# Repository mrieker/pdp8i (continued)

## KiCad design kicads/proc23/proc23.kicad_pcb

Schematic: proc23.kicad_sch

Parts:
J1, J2, J3, J4: Conn_01x36; PinHeader_1x36_P2.54mm_Vertical
U1, U11, U17, U18, U19, U35, U37, U46, U49, U50, U162, U163, U169: 74AHC540; DIP-20_W7.62mm
U8, U106, U119, U123, U124, U125, U128, U141: 74AHC04; DIP-14_W7.62mm
U21, U140: 74AHC138; DIP-16_W7.62mm
U27, U142, U144: 74AHC02; DIP-14_W7.62mm
U44, U82, U91, U107, U108, U109, U113, U120, U127, U147, U151, U156, U158, U161, U168: 74AHC00; DIP-14_W7.62mm
U54, U55, U56, U74, U77, U80: 74AHC08; DIP-14_W7.62mm
U57: 74AC11; DIP-14_W7.62mm
U58, U59, U60, U89: 74AHC86; DIP-14_W7.62mm
U61, U62, U65, U66, U69, U70, U83, U84, U85, U86, U87, U88: 74AC153; DIP-16_W7.62mm
U63, U64, U67: 74AHC157; DIP-16_W7.62mm
U68, U71, U116, U157, U165: 74HC30; DIP-14_W7.62mm
U73, U76, U79, U110: 74AHC32; DIP-14_W7.62mm
U75, U78, U81: 74AC283; DIP-16_W7.62mm
U90: 74AHC74
U92, U93, U94, U95, U96, U97, U98, U99, U100, U101, U102, U103, U104: 74AC151; DIP-16_W7.62mm
U105, U111, U112, U143, U146, U148, U149, U150, U159, U160: 74AC10; DIP-14_W7.62mm
U114: 74HC42; DIP-16_W7.62mm
U117, U118, U121, U122, U153, U164: 74AC20; DIP-14_W7.62mm
U126: 74AHC08
U129, U130, U131, U132, U136, U137: 74AHC174; DIP-16_W7.62mm
U133, U134, U135: 74AC161; DIP-16_W7.62mm
U138: 74AHC74; DIP-14_W7.62mm
U139: 74AC175; DIP-16_W7.62mm
U145, U152, U154, U170: 74HC27; DIP-14_W7.62mm
U155: 74HC21; DIP-14_W7.62mm
U171: 74HC4075; DIP-14_W7.62mm

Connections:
/AA: U27.2, U161.6, U170.9
/BB: U68.8, U125.11, U144.8
/CC: U144.9, U148.8
/CC3: U128.4, U168.9, U171.1
/CONSCK: J4.35
/CONSDA: J4.34
/EE: U27.8, U160.8
/FF: U27.9, U142.5, U144.6, U153.8
/HH: U106.12, U170.1, U170.3
/JJ: U142.6, U144.5, U165.8, U170.2, U170.4
/KK: U128.10, U170.10
/LL: U118.6, U170.13
/MM: U159.12, U170.5
/NN: U119.2, U156.9, U170.11
/PP: U161.11
/_AA1: U143.12, U161.4
/_AA2: U127.8, U161.5
/_ACCLEAR: J3.28, U50.4 (A2)
/_ACUM_0: J3.7, U46.16 (Y2)
/_ACUM_1: J2.34, U37.13 (Y5)
/_ACUM_2: J2.27, U37.18 (Y0)
/_ACUM_3: J2.20, U35.15 (Y3)
/_ACUM_4: J2.13, U19.12 (Y6)
/_ACUM_5: J2.7, U19.17 (Y1)
/_ACUM_6: J1.35, U18.14 (Y4)
/_ACUM_7: J1.29, U17.11 (Y7)
/_ACUM_8: J1.23, U17.16 (Y2)
/_ACUM_9: J1.16, U11.14 (Y4)
/_ACUM_10: J1.9, U1.12 (Y6)
/_ACUM_11: J1.2, U1.18 (Y0)
/_BB1: U68.3, U123.2
/_BB2: U68.4, U119.10
/_BB3: U68.5, U146.8
/_BB4: U68.6, U147.3
/_BB5: U68.11, U110.8
/_BB6: U68.12, U171.6
/_BRKCYC: J4.33, U163.11 (Y7)
/_BRKGNTI: J4.32
/_BRKGNTO: J4.31
/_BRKRQST: J3.29
/_BRKWRM: J4.11, U50.6 (A4)
/_BUSINI: J3.31, U163.3 (A1)
/_BWCOV: J3.32, U163.16 (Y2)
/_CAINC: J4.12, U50.7 (A5)
/_CC1: U109.11, U148.9, U168.12
/_CC2: U147.8, U148.10, U168.13
/_CC3: U110.4, U111.6, U128.3, U148.11
/_CLOCK: J4.6, U50.2 (A0)
/_CYCLE3: J4.13, U50.8 (A6)
/_DFLD_0: J3.22
/_DFLD_1: J3.18
/_DFLD_2: J3.14
/_DMAFLD_0: J3.23
/_DMAFLD_1: J3.19
/_DMAFLD_2: J3.15
/_EE1: U149.6, U160.9
/_EE2: U148.6, U160.10
/_EE3: U147.11, U160.11
/_FF1: U150.12, U153.9
/_FF2: U150.6, U153.10
/_FF3: U151.8, U153.12
/_FF4: U149.12, U153.13
/_HH1: U106.13, U142.1
/_IFLD_0: J3.24
/_IFLD_1: J3.20
/_IFLD_2: J3.16
/_INBUS_0: J3.10, U46.7 (A5)
/_INBUS_1: J3.3, U46.2 (A0)
/_INBUS_2: J2.30, U37.5 (A3)
/_INBUS_3: J2.23, U35.8 (A6)
/_INBUS_4: J2.16, U35.3 (A1)
/_INBUS_5: J2.10, U19.6 (A4)
/_INBUS_6: J2.4, U18.9 (A7)
/_INBUS_7: J1.32, U18.4 (A2)
/_INBUS_8: J1.26, U17.7 (A5)
/_INBUS_9: J1.19, U11.9 (A7)
/_INBUS_10: J1.12, U11.3 (A1)
/_INBUS_11: J1.5, U1.5 (A3)
/_INTINH: J4.15
/_INTRQST: J4.16
/_ION: J3.30, U163.2 (A0)
/_IOP: J4.8, U163.5 (A3)
/_IOSKIP: J4.17, U162.4 (A2)
/_IREG_9: J1.22, U17.17 (Y1)
/_IREG_10: J1.15, U11.15 (Y3)
/_IREG_11: J1.8, U1.13 (Y5)
/_JJ1: U127.6, U165.3
/_JJ2: U151.11, U165.4
/_JJ3: U146.6, U165.5
/_JJ4: U158.3, U165.6
/_JJ5: U158.6, U165.11
/_JJ6: U44.3, U165.12
/_KK1: U128.11, U159.6
/_LINK: J4.9, U163.14 (Y4)
/_LL1: U118.1, U146.12
/_LL2: U118.2, U158.8
/_LL3: U118.4, U158.11
/_LL4: U118.5, U160.12
/_LNKTOG: J4.18, U162.5 (A3)
/_MADR_0: J3.8, U46.15 (Y3)
/_MADR_1: J2.35, U37.12 (Y6)
/_MADR_2: J2.28, U37.17 (Y1)
/_MADR_3: J2.21, U35.14 (Y4)
/_MADR_4: J2.14, U19.11 (Y7)
/_MADR_5: J2.8, U19.16 (Y2)
/_MADR_6: J2.2, U18.13 (Y5)
/_MADR_7: J1.30, U18.18 (Y0)
/_MADR_8: J1.24, U17.15 (Y3)
/_MADR_9: J1.17, U11.13 (Y5)
/_MADR_10: J1.10, U1.11 (Y7)
/_MADR_11: J1.3, U1.17 (Y1)
/_MAJST_0: J4.22, U162.6 (A4)
/_MAJST_1: J4.21, U162.7 (A5)
/_MAJST_2: J4.20, U162.8 (A6)
/_MAJST_3: J4.19, U162.9 (A7)
/_MBUF_0: J3.9, U46.14 (Y4)
/_MBUF_1: J3.2, U37.11 (Y7)
/_MBUF_2: J2.29, U37.16 (Y2)
/_MBUF_3: J2.22, U35.13 (Y5)
/_MBUF_4: J2.15, U35.18 (Y0)
/_MBUF_5: J2.9, U19.15 (Y3)
/_MBUF_6: J2.3, U18.12 (Y6)
/_MBUF_7: J1.31, U18.17 (Y1)
/_MBUF_8: J1.25, U17.14 (Y4)
/_MBUF_9: J1.18, U11.12 (Y6)
/_MBUF_10: J1.11, U11.18 (Y0)
/_MBUF_11: J1.4, U1.16 (Y2)
/_MEAD_0: J3.25
/_MEAD_1: J3.21
/_MEAD_2: J3.17
/_MEMDIS: J3.26
/_MM1: U150.8, U159.1
/_MM2: U159.2, U161.3
/_MM3: U122.8, U159.13
/_MQUO_0: J3.11
/_MQUO_1: J3.4
/_MQUO_2: J2.31
/_MQUO_3: J2.24
/_MQUO_4: J2.17
/_MQUO_5: J2.11
/_MQUO_6: J2.5
/_MQUO_7: J1.33
/_MQUO_8: J1.27
/_MQUO_9: J1.20
/_MQUO_10: J1.13
/_MQUO_11: J1.6
/_NN1: U105.4, U119.1, U149.8
/_PAUSE: J4.14
/_PCTR_0: J3.12, U46.12 (Y6)
/_PCTR_1: J3.5, U46.17 (Y1)
/_PCTR_2: J2.32, U37.14 (Y4)
/_PCTR_3: J2.25, U35.11 (Y7)
/_PCTR_4: J2.18, U35.16 (Y2)
/_PCTR_5: J2.12, U19.13 (Y5)
/_PCTR_6: J2.6, U19.18 (Y0)
/_PCTR_7: J1.34, U18.15 (Y3)
/_PCTR_8: J1.28, U17.12 (Y6)
/_PCTR_9: J1.21, U17.18 (Y0)
/_PCTR_10: J1.14, U11.16 (Y2)
/_PCTR_11: J1.7, U1.14 (Y4)
/_PP1: U119.5, U159.8, U161.12
/_PP2: U105.3, U160.6, U161.13
/_READSR: J3.27, U46.11 (Y7)
/_RESET: J4.7, U50.3 (A1)
/_RUN: J4.10, U163.7 (A5)
/_SWCONT: J4.2, U49.5 (A3)
/_SWDEPOS: J3.35, U49.4 (A2)
/_SWEXAM: J3.34, U49.3 (A1)
/_SWLDAD: J3.33, U49.2 (A0)
/_SWSINST: J4.5
/_SWSSTEP: J4.4
/_SWSTART: J4.3, U49.6 (A4)
/_TP1: J4.27, U169.6 (A4)
/_TP2: J4.28, U169.7 (A5)
/_TP3: J4.29, U169.8 (A6)
/_TP4: J4.30, U169.9 (A7)
/_TS1: J4.23, U169.2 (A0)
/_TS2: J4.24, U169.3 (A1)
/_TS3: J4.25, U169.4 (A2)
/_TS4: J4.26, U169.5 (A3)
/_asel_0: U61.14 (S0), U62.14 (S0), U65.14 (S0), U66.14 (S0), U69.14 (S0), U70.14 (S0), U164.4, U170.12
/_asel_1: U61.2 (S1), U62.2 (S1), U65.2 (S1), U66.2 (S1), U69.2 (S1), U70.2 (S1), U164.5, U170.6
/_bsel_0: U63.1 (S), U64.1 (S), U67.1 (S), U144.10
/_clock: U8.4
/_extarex: U44.10, U112.11, U119.12, U121.13
/_irand: U140.15 (~Y0), U141.13, U143.9
/_irdca: U105.10, U140.12 (~Y3), U141.5, U143.11
/_iriot: U140.9 (~Y6)
/_irisz: U105.9, U140.13 (~Y2), U141.9
/_irjmp: U140.10 (~Y5), U141.1, U142.8
/_irjms: U105.11, U140.11 (~Y4), U141.3
/_iropr: U106.5, U122.13, U140.7 (~Y7), U144.2, U145.1
/_irtad: U140.14 (~Y1), U141.11, U143.10
/_ldadclk: U82.12, U111.1, U161.8
/_msdefer: U114.3 (2), U123.11
/_msdepos: U114.10 (8), U116.12, U124.11
/_msexec: U82.1, U114.4 (3), U123.13
/_msintak: U114.9 (7), U116.11, U118.13, U124.9
/_mswrdct: U82.2, U114.5 (4), U116.4, U124.1
/_nxtmsbreak: U21.9 (~Y6), U171.4
/_nxtmswrdct: U21.11 (~Y4), U110.10
/_pcld: U56.3, U133.9 (~PE), U134.9 (~PE), U135.9 (~PE)
/_reset: U8.6, U138.13 (~R)
/_rsel_0: U91.6, U92.11 (S0), U93.11 (S0), U94.11 (S0), U95.11 (S0), U96.11 (S0), U97.11 (S0), U98.11 (S0), U99.11 (S0), U100.11 (S0), U101.11 (S0), U102.11 (S0), U103.11 (S0), U104.11 (S0)
/_rsel_1: U91.8, U92.10 (S1), U93.10 (S1), U94.10 (S1), U95.10 (S1), U96.10 (S1), U97.10 (S1), U98.10 (S1), U99.10 (S1), U100.10 (S1), U101.10 (S1), U102.10 (S1), U103.10 (S1), U104.10 (S1)
/_rsel_2: U91.11, U92.9 (S2), U93.9 (S2), U94.9 (S2), U95.9 (S2), U96.9 (S2), U97.9 (S2), U98.9 (S2), U99.9 (S2), U100.9 (S2), U101.9 (S2), U102.9 (S2), U103.9 (S2), U104.9 (S2)
/_ts4: U110.9, U128.6, U171.3
/acclear: U50.16 (Y2), U168.5
/acclk: U56.8, U136.9 (Cp), U137.9 (Cp)
/acum_0: U46.4 (A2), U58.1, U136.2 (Q0), U152.11
/acum_1: U37.7 (A5), U58.4, U136.5 (Q1), U152.10
/acum_2: U37.2 (A0), U58.9, U136.7 (Q2), U152.9
/acum_3: U35.5 (A3), U58.12, U136.10 (Q3), U154.11
/acum_4: U19.8 (A6), U59.1, U136.12 (Q4), U154.10
/acum_5: U19.3 (A1), U59.4, U136.15 (Q5), U154.9
/acum_6: U18.6 (A4), U59.9, U137.2 (Q0), U154.5
/acum_7: U17.9 (A7), U59.12, U137.5 (Q1), U154.4
/acum_8: U17.4 (A2), U60.1, U137.7 (Q2), U154.3
/acum_9: U11.6 (A4), U60.4, U137.10 (Q3), U154.13
/acum_10: U1.8 (A6), U60.9, U137.12 (Q4), U154.2
/acum_11: U1.2 (A0), U60.12, U127.12, U137.15 (Q5), U154.1
/acxx_0: U58.3, U61.3 (I3a)
/acxx_1: U58.6, U61.13 (I3b)
/acxx_2: U58.8, U62.3 (I3a)
/acxx_3: U58.11, U62.13 (I3b)
/acxx_4: U59.3, U65.3 (I3a)
/acxx_5: U59.6, U65.13 (I3b)
/acxx_6: U59.8, U66.3 (I3a)
/acxx_7: U59.11, U66.13 (I3b)
/acxx_8: U60.3, U69.3 (I3a)
/acxx_9: U60.6, U69.13 (I3b)
/acxx_10: U60.8, U70.3 (I3a)
/acxx_11: U60.11, U70.13 (I3b)
/alua_0: U61.7 (Za), U73.1, U74.1, U75.5 (A1)
/alua_1: U61.9 (Zb), U73.4, U74.4, U75.3 (A2)
/alua_2: U62.7 (Za), U73.9, U74.9, U75.14 (A3)
/alua_3: U62.9 (Zb), U73.12, U74.12, U75.12 (A4)
/alua_4: U65.7 (Za), U76.1, U77.1, U78.5 (A1)
/alua_5: U65.9 (Zb), U76.4, U77.4, U78.3 (A2)
/alua_6: U66.7 (Za), U76.9, U77.9, U78.14 (A3)
/alua_7: U66.9 (Zb), U76.12, U77.12, U78.12 (A4)
/alua_8: U69.7 (Za), U79.1, U80.1, U81.5 (A1)
/alua_9: U69.9 (Zb), U79.4, U80.4, U81.3 (A2)
/alua_10: U70.7 (Za), U79.9, U80.9, U81.14 (A3)
/alua_11: U70.9 (Zb), U79.12, U80.12, U81.12 (A4)
/alub_0: U63.4 (Za), U73.2, U74.2, U75.6 (B1)
/alub_1: U63.7 (Zb), U73.5, U74.5, U75.2 (B2)
/alub_2: U63.9 (Zc), U73.10, U74.10, U75.15 (B3)
/alub_3: U63.12 (Zd), U73.13, U74.13, U75.11 (B4)
/alub_4: U64.4 (Za), U76.2, U77.2, U78.6 (B1)
/alub_5: U64.7 (Zb), U76.5, U77.5, U78.2 (B2)
/alub_6: U64.9 (Zc), U76.10, U77.10, U78.15 (B3)
/alub_7: U64.12 (Zd), U76.13, U77.13, U78.11 (B4)
/alub_8: U67.4 (Za), U79.2, U80.2, U81.6 (B1)
/alub_9: U67.7 (Zb), U79.5, U80.5, U81.2 (B2)
/alub_10: U67.9 (Zc), U79.10, U80.10, U81.15 (B3)
/alub_11: U67.12 (Zd), U79.13, U80.13, U81.11 (B4)
/aluq_0: U83.7 (Za), U92.12 (I7), U93.14 (I5), U94.15 (I4), U98.13 (I6), U103.2 (I2), U104.1 (I3), U129.3 (D0), U131.3 (D0), U133.3 (D0)
/aluq_1: U83.9 (Zb), U92.1 (I3), U93.12 (I7), U94.14 (I5), U95.15 (I4), U99.13 (I6), U104.2 (I2), U129.4 (D1), U131.4 (D1), U133.4 (D1)
/aluq_2: U84.7 (Za), U92.2 (I2), U93.1 (I3), U94.12 (I7), U95.14 (I5), U96.15 (I4), U100.13 (I6), U129.6 (D2), U131.6 (D2), U133.5 (D2)
/aluq_3: U84.9 (Zb), U93.2 (I2), U94.1 (I3), U95.12 (I7), U96.14 (I5), U97.15 (I4), U101.13 (I6), U129.11 (D3), U131.11 (D3), U133.6 (D3)
/aluq_4: U85.7 (Za), U94.2 (I2), U95.1 (I3), U96.12 (I7), U97.14 (I5), U98.15 (I4), U102.13 (I6), U129.13 (D4), U131.13 (D4), U134.3 (D0)
/aluq_5: U85.9 (Zb), U95.2 (I2), U96.1 (I3), U97.12 (I7), U98.14 (I5), U99.15 (I4), U103.13 (I6), U129.14 (D5), U131.14 (D5), U134.4 (D1)
/aluq_6: U86.7 (Za), U92.13 (I6), U96.2 (I2), U97.1 (I3), U98.12 (I7), U99.14 (I5), U100.15 (I4), U130.3 (D0), U132.3 (D0), U134.5 (D2)
/aluq_7: U86.9 (Zb), U93.13 (I6), U97.2 (I2), U98.1 (I3), U99.12 (I7), U100.14 (I5), U101.15 (I4), U130.4 (D1), U132.4 (D1), U134.6 (D3)
/aluq_8: U87.7 (Za), U94.13 (I6), U98.2 (I2), U99.1 (I3), U100.12 (I7), U101.14 (I5), U102.15 (I4), U130.6 (D2), U132.6 (D2), U135.3 (D0)
/aluq_9: U87.9 (Zb), U95.13 (I6), U99.2 (I2), U100.1 (I3), U101.12 (I7), U102.14 (I5), U103.15 (I4), U130.11 (D3), U132.11 (D3), U135.4 (D1)
/aluq_10: U88.7 (Za), U96.13 (I6), U100.2 (I2), U101.1 (I3), U102.12 (I7), U103.14 (I5), U104.15 (I4), U130.13 (D4), U132.13 (D4), U135.5 (D2)
/aluq_11: U88.9 (Zb), U92.15 (I4), U97.13 (I6), U101.2 (I2), U102.1 (I3), U103.12 (I7), U104.14 (I5), U130.14 (D5), U132.14 (D5), U135.6 (D3)
/aluq_12: U89.3, U92.14 (I5), U93.15 (I4), U102.2 (I2), U103.1 (I3), U104.12 (I7), U104.13 (I6)
/autoinc: U107.5, U150.13, U155.6
/azero: U61.1 (Ea), U61.15 (Eb), U62.1 (Ea), U62.15 (Eb), U65.1 (Ea), U65.15 (Eb), U66.1 (Ea), U66.15 (Eb), U69.1 (Ea), U69.15 (Eb), U70.1 (Ea), U70.15 (Eb), U148.12
/brkcyc: U138.9 (Q), U163.9 (A7)
/brkwrm: U50.14 (Y4), U109.2, U146.11
/busini: U125.13, U163.17 (Y1)
/bwcov: U90.5 (Q), U112.13, U163.4 (A2)
/bzero: U63.15 (E), U64.15 (E), U67.15 (E), U164.6
/cainc: U50.13 (Y5), U108.13, U149.13
/cclears: U27.3, U168.3
/cin: U75.7 (C0), U156.6
/clock: U8.3, U50.18 (Y0)
/comac: U57.8, U58.2, U58.5, U58.10, U58.13, U59.2, U59.5, U59.10, U59.13, U60.2, U60.5, U60.10, U60.13
/comln: U57.6, U89.4
/cout: U81.9 (C4), U89.1, U90.2 (D)
/cycle3: U50.12 (Y6), U171.5
/dirjmp: U113.5, U142.10, U150.11
/efaddr_7: U55.11, U66.11 (I1b)
/efaddr_8: U55.8, U69.5 (I1a)
/efaddr_9: U55.6, U69.11 (I1b)
/efaddr_10: U55.3, U70.5 (I1a)
/efaddr_11: U56.11, U70.11 (I1b)
/extarex: U44.4, U119.13, U147.10, U156.11
/g2skip: U89.8, U111.11
/group1: U57.2, U57.4, U57.10, U82.10, U110.12, U121.4, U122.4, U144.1, U149.11
/group2: U110.13, U111.5, U111.10, U145.12
/inbus_0: U46.13 (Y5), U63.2 (I0a)
/inbus_1: U46.18 (Y0), U63.5 (I0b)
/inbus_2: U37.15 (Y3), U63.11 (I0c)
/inbus_3: U35.12 (Y6), U63.14 (I0d)
/inbus_4: U35.17 (Y1), U64.2 (I0a)
/inbus_5: U19.14 (Y4), U64.5 (I0b)
/inbus_6: U18.11 (Y7), U64.11 (I0c)
/inbus_7: U18.16 (Y2), U64.14 (I0d)
/inbus_8: U17.13 (Y5), U67.2 (I0a), U139.4 (D0)
/inbus_9: U11.11 (Y7), U67.5 (I0b), U139.5 (D1)
/inbus_10: U11.17 (Y1), U67.11 (I0c), U139.12 (D2)
/inbus_11: U1.15 (Y3), U67.14 (I0d), U128.13
/ion: U163.18 (Y0)
/iop: U108.4, U109.13, U119.3, U163.15 (Y3)
/ioskip: U108.5, U112.5, U162.16 (Y2)
/irand: U141.12, U159.11
/irandtaddca: U109.10, U143.8
/irdca: U141.6, U143.13, U159.5
/ireg_8: U139.2 (Q0)
/ireg_9: U17.3 (A1), U139.7 (Q1), U140.1 (A0)
/ireg_10: U11.5 (A3), U139.10 (Q2), U140.2 (A1)
/ireg_11: U1.7 (A5), U139.14 (~Q3), U140.3 (A2)
/irisz: U112.2, U141.8, U150.5
/irjmp: U113.2, U141.2, U149.5
/irjms: U113.10, U141.4, U146.5, U146.13
/iropr: U71.3, U106.6, U112.4, U151.4, U160.13
/irtad: U91.2, U141.10, U160.5
/link: U89.5, U138.5 (Q), U151.1, U163.6 (A4)
/lnclk: U56.6, U138.3 (C)
/lndat: U44.11, U138.2 (D)
/lnktog: U44.5, U162.15 (Y3)
/madr_0: U46.5 (A3), U61.6 (I0a), U129.2 (Q0)
/madr_1: U37.8 (A6), U61.10 (I0b), U129.5 (Q1)
/madr_2: U37.3 (A1), U62.6 (I0a), U129.7 (Q2)
/madr_3: U35.6 (A4), U62.10 (I0b), U129.10 (Q3), U155.5
/madr_4: U19.9 (A7), U65.6 (I0a), U129.12 (Q4), U142.12
/madr_5: U19.4 (A2), U65.10 (I0b), U129.15 (Q5), U142.11
/madr_6: U18.7 (A5), U66.6 (I0a), U130.2 (Q0), U152.5
/madr_7: U18.2 (A0), U55.13, U66.10 (I0b), U130.5 (Q1), U152.4
/madr_8: U17.5 (A3), U55.10, U69.6 (I0a), U130.7 (Q2), U152.3
/madr_9: U11.7 (A5), U55.5, U69.10 (I0b), U130.10 (Q3), U152.13
/madr_10: U1.9 (A7), U55.2, U70.6 (I0a), U130.12 (Q4), U152.2
/madr_11: U1.3 (A1), U56.13, U70.10 (I0b), U130.15 (Q5), U152.1
/majst_0: U114.15 (A0), U162.14 (Y4)
/majst_1: U114.14 (A1), U162.13 (Y5)
/majst_2: U114.13 (A2), U162.12 (Y6)
/majst_3: U114.12 (A3), U123.3, U144.11, U162.11 (Y7)
/maload: U82.11, U129.9 (Cp), U130.9 (Cp)
/mbload: U108.3, U131.9 (Cp), U132.9 (Cp)
/mbuf_0: U46.6 (A4), U61.5 (I1a), U63.3 (I1a), U71.12, U131.2 (Q0), U145.13, U156.10
/mbuf_1: U8.1, U37.9 (A7), U61.11 (I1b), U63.6 (I1b), U91.5, U131.5 (Q1)
/mbuf_2: U37.4 (A2), U62.5 (I1a), U63.10 (I1c), U91.10, U106.11, U110.5, U131.7 (Q2)
/mbuf_3: U35.7 (A5), U62.11 (I1b), U63.13 (I1d), U89.10, U91.13, U131.10 (Q3)
/mbuf_4: U35.2 (A0), U57.5, U64.3 (I1a), U65.5 (I1a), U131.12 (Q4), U151.2
/mbuf_5: U19.5 (A3), U57.9, U64.6 (I1b), U65.11 (I1b), U131.15 (Q5), U157.12
/mbuf_6: U18.8 (A6), U64.10 (I1c), U66.5 (I1a), U122.5, U127.13, U132.2 (Q0)
/mbuf_7: U18.3 (A1), U55.1, U55.4, U55.9, U55.12, U56.12, U64.13 (I1d), U121.5, U132.5 (Q1), U168.10
/mbuf_8: U17.6 (A4), U67.3 (I1a), U71.5, U128.9, U132.7 (Q2), U142.9, U144.3
/mbuf_9: U11.8 (A6), U67.6 (I1b), U132.10 (Q3)
/mbuf_10: U11.2 (A0), U67.10 (I1c), U132.12 (Q4)
/mbuf_11: U1.4 (A2), U67.13 (I1d), U132.15 (Q5)
/memacsw: J2.19, U161.9
/msbreak: U109.1, U124.6, U146.10, U147.4
/mscurad: U108.12, U124.4, U147.13, U149.2
/msdefer: U107.4, U113.1, U123.10, U148.5, U149.4, U150.2
/msdepos: U54.9, U107.13, U124.10, U147.2, U151.13
/msexam: U107.10, U124.12, U127.5
/msexec: U91.1, U107.1, U109.9, U112.1, U112.3, U113.9, U123.12, U143.2, U146.2, U146.4, U150.4, U151.5, U159.4, U159.10, U160.4
/msfetch: U57.11, U57.13, U71.4, U82.9, U109.4, U111.4, U111.9, U113.4, U120.5, U120.13, U121.2, U122.2, U122.12, U123.8, U126.2, U149.10, U150.10
/msintak: U124.8, U127.2, U158.2, U158.10
/mspwron: U123.6
/mswrdct: U44.2, U124.2, U151.10, U158.5
/nxtms_0: J3.13, U21.1 (A0)
/nxtms_1: J3.6, U21.2 (A1)
/nxtms_2: J2.33, U21.3 (A2)
/nxtms_3: J2.26, U21.4 (~E0)
/nxtmsdefer: U125.6, U161.2
/nxtmsexec: U122.10, U125.8, U148.4, U160.2
/nxtmsfetch: U125.4, U158.13
/nxtmsintak: U119.8, U127.10
/nxtmspwron: U125.2
/pcclk: U111.12, U133.2 (CP), U134.2 (CP), U135.2 (CP)
/pcinc: U113.11, U133.7 (CEP), U133.10 (CET), U134.7 (CEP), U135.7 (CEP)
/pctr_0: U46.8 (A6), U61.4 (I2a), U133.14 (Q0)
/pctr_1: U46.3 (A1), U61.12 (I2b), U133.13 (Q1)
/pctr_2: U37.6 (A4), U62.4 (I2a), U133.12 (Q2)
/pctr_3: U35.9 (A7), U62.12 (I2b), U133.11 (Q3)
/pctr_4: U35.4 (A2), U65.4 (I2a), U134.14 (Q0)
/pctr_5: U19.7 (A5), U65.12 (I2b), U134.13 (Q1)
/pctr_6: U19.2 (A0), U66.4 (I2a), U134.12 (Q2)
/pctr_7: U18.5 (A3), U66.12 (I2b), U134.11 (Q3)
/pctr_8: U17.8 (A6), U69.4 (I2a), U135.14 (Q0)
/pctr_9: U17.2 (A0), U69.12 (I2b), U135.13 (Q1)
/pctr_10: U11.4 (A2), U70.4 (I2a), U135.12 (Q2)
/pctr_11: U1.6 (A4), U70.12 (I2b), U135.11 (Q3)
/qsel_0: U83.14 (S0), U84.14 (S0), U85.14 (S0), U86.14 (S0), U87.14 (S0), U88.14 (S0), U119.6
/qsel_1: U83.2 (S1), U84.2 (S1), U85.2 (S1), U86.2 (S1), U87.2 (S1), U88.2 (S1), U105.6
/qsum_0: U75.4 (S1), U83.4 (I2a)
/qsum_1: U75.1 (S2), U83.12 (I2b)
/qsum_2: U75.13 (S3), U84.4 (I2a)
/qsum_3: U75.10 (S4), U84.12 (I2b)
/readsr: U46.9 (A7), U171.9
/reset: U8.5, U50.17 (Y1)
/rotq_0: U92.5 (Z), U136.3 (D0)
/rotq_1: U93.5 (Z), U136.4 (D1)
/rotq_2: U94.5 (Z), U136.6 (D2)
/rotq_3: U95.5 (Z), U136.11 (D3)
/rotq_4: U96.5 (Z), U136.13 (D4)
/rotq_5: U97.5 (Z), U136.14 (D5)
/rotq_6: U98.5 (Z), U137.3 (D0)
/rotq_7: U99.5 (Z), U137.4 (D1)
/rotq_8: U100.5 (Z), U137.6 (D2)
/rotq_9: U101.5 (Z), U137.11 (D3)
/rotq_10: U102.5 (Z), U137.13 (D4)
/rotq_11: U103.5 (Z), U137.14 (D5)
/rotq_12: U44.9, U104.5 (Z)
/run: U56.1, U163.13 (Y5)
/swcont: U49.15 (Y3), U128.1
/swcontx: U142.3, U144.13
/swdepos: U49.16 (Y2), U107.12, U151.12
/swexam: U49.17 (Y1), U107.9, U127.4
/swldad: U49.18 (Y0), U106.9, U123.1, U171.2
/swstart: U49.14 (Y4), U142.2
/tp1: U106.3, U126.1, U127.1, U169.14 (Y4)
/tp2: U54.4, U108.9, U120.4, U121.1, U122.1, U169.13 (Y5)
/tp3: U56.4, U56.9, U106.1, U169.12 (Y6)
/tp4: U82.4, U169.11 (Y7)
/ts1: U119.11, U147.5, U169.18 (Y0)
/ts2: U54.10, U120.12, U146.1, U146.9, U147.1, U149.1, U150.1, U150.3, U151.9, U158.9, U159.3, U169.17 (Y1)
/ts3: U57.1, U57.3, U109.12, U111.3, U120.1, U120.9, U143.1, U146.3, U147.9, U149.3, U149.9, U150.9, U158.1, U158.4, U159.9, U160.3, U169.16 (Y2)
/ts4: U44.1, U122.9, U127.9, U128.5, U138.11 (C), U147.12, U148.3, U158.12, U160.1, U161.1, U169.15 (Y3)
GND: J1.36, J2.36, J3.36, J4.36, U1.1 (G1), U1.10 (GND), U1.19 (G2), U8.7 (GND), U11.1 (G1), U11.10 (GND), U11.19 (G2), U17.1 (G1), U17.10 (GND), U17.19 (G2), U18.1 (G1), U18.10 (GND), U18.19 (G2), U19.1 (G1), U19.10 (GND), U19.19 (G2), U21.5 (~E1), U21.8 (GND), U27.7 (GND), U35.1 (G1), U35.10 (GND), U35.19 (G2), U37.1 (G1), U37.10 (GND), U37.19 (G2), U44.7 (GND), U46.1 (G1), U46.10 (GND), U46.19 (G2), U49.1 (G1), U49.10 (GND), U49.19 (G2), U50.1 (G1), U50.10 (GND), U50.19 (G2), U54.7 (GND), U55.7 (GND), U56.7 (GND), U57.7 (GND), U58.7 (GND), U59.7 (GND), U60.7 (GND), U61.8 (GND), U62.8 (GND), U63.8 (GND), U64.8 (GND), U65.8 (GND), U66.8 (GND), U67.8 (GND), U68.7 (GND), U69.8 (GND), U70.8 (GND), U71.7 (GND), U73.7 (GND), U74.7 (GND), U75.8 (GND), U76.7 (GND), U77.7 (GND), U78.8 (GND), U79.7 (GND), U80.7 (GND), U81.8 (GND), U82.7 (GND), U83.1 (Ea), U83.3 (I3a), U83.8 (GND), U83.13 (I3b), U83.15 (Eb), U84.1 (Ea), U84.3 (I3a), U84.8 (GND), U84.13 (I3b), U84.15 (Eb), U85.1 (Ea), U85.3 (I3a), U85.8 (GND), U85.13 (I3b), U85.15 (Eb), U86.1 (Ea), U86.3 (I3a), U86.8 (GND), U86.13 (I3b), U86.15 (Eb), U87.1 (Ea), U87.3 (I3a), U87.8 (GND), U87.13 (I3b), U87.15 (Eb), U88.1 (Ea), U88.3 (I3a), U88.8 (GND), U88.13 (I3b), U88.15 (Eb), U89.7 (GND), U90.7 (GND), U91.7 (GND), U92.3 (I1), U92.4 (I0), U92.7 (~E), U92.8 (GND), U93.3 (I1), U93.4 (I0), U93.7 (~E), U93.8 (GND), U94.3 (I1), U94.4 (I0), U94.7 (~E), U94.8 (GND), U95.3 (I1), U95.4 (I0), U95.7 (~E), U95.8 (GND), U96.3 (I1), U96.4 (I0), U96.7 (~E), U96.8 (GND), U97.3 (I1), U97.4 (I0), U97.7 (~E), U97.8 (GND), U98.3 (I1), U98.4 (I0), U98.7 (~E), U98.8 (GND), U99.3 (I1), U99.4 (I0), U99.7 (~E), U99.8 (GND), U100.3 (I1), U100.4 (I0), U100.7 (~E), U100.8 (GND), U101.3 (I1), U101.4 (I0), U101.7 (~E), U101.8 (GND), U102.3 (I1), U102.4 (I0), U102.7 (~E), U102.8 (GND), U103.3 (I1), U103.4 (I0), U103.7 (~E), U103.8 (GND), U104.3 (I1), U104.4 (I0), U104.7 (~E), U104.8 (GND), U105.7 (GND), U106.7 (GND), U107.7 (GND), U108.7 (GND), U109.7 (GND), U110.7 (GND), U111.7 (GND), U112.7 (GND), U113.7 (GND), U114.8 (GND), U116.7 (GND), U117.7 (GND), U118.7 (GND), U119.7 (GND), U120.7 (GND), U121.7 (GND), U122.7 (GND), U123.7 (GND), U124.7 (GND), U125.7 (GND), U126.7 (GND), U127.7 (GND), U128.7 (GND), U129.8 (GND), U130.8 (GND), U131.8 (GND), U132.8 (GND), U133.8 (GND), U134.8 (GND), U135.8 (GND), U136.8 (GND), U137.8 (GND), U138.7 (GND), U138.12 (D), U139.8 (GND), U140.4 (~E0), U140.5 (~E1), U140.8 (GND), U141.7 (GND), U142.7 (GND), U143.7 (GND), U144.7 (GND), U145.7 (GND), U146.7 (GND), U147.7 (GND), U148.7 (GND), U149.7 (GND), U150.7 (GND), U151.7 (GND), U152.7 (GND), U153.7 (GND), U154.7 (GND), U155.7 (GND), U156.7 (GND), U157.7 (GND), U158.7 (GND), U159.7 (GND), U160.7 (GND), U161.7 (GND), U162.1 (G1), U162.10 (GND), U162.19 (G2), U163.1 (G1), U163.10 (GND), U163.19 (G2), U164.7 (GND), U165.7 (GND), U168.7 (GND), U169.1 (G1), U169.10 (GND), U169.19 (G2), U170.7 (GND), U171.7 (GND)
unnamed: U21.15 (~Y0), U125.1
unnamed: U21.14 (~Y1), U125.3
unnamed: U21.13 (~Y2), U125.5
unnamed: U21.12 (~Y3), U125.9
unnamed: U21.7 (~Y7), U119.9
unnamed: U44.8, U44.12
unnamed: U44.6, U44.13
unnamed: U54.5, U82.3
unnamed: U57.12, U91.4, U91.9, U91.12
unnamed: U8.2, U71.11
unnamed: U75.9 (C4), U78.7 (C0)
unnamed: U78.9 (C4), U81.7 (C0)
unnamed: U78.4 (S1), U85.4 (I2a)
unnamed: U78.1 (S2), U85.12 (I2b)
unnamed: U78.13 (S3), U86.4 (I2a)
unnamed: U78.10 (S4), U86.12 (I2b)
unnamed: U81.4 (S1), U87.4 (I2a)
unnamed: U81.1 (S2), U87.12 (I2b)
unnamed: U81.13 (S3), U88.4 (I2a)
unnamed: U81.10 (S4), U88.12 (I2b)
unnamed: U82.6, U82.13
unnamed: U73.3, U83.6 (I0a)
unnamed: U73.6, U83.10 (I0b)
unnamed: U74.3, U83.5 (I1a)
unnamed: U74.6, U83.11 (I1b)
unnamed: U73.8, U84.6 (I0a)
unnamed: U73.11, U84.10 (I0b)
unnamed: U74.8, U84.5 (I1a)
unnamed: U74.11, U84.11 (I1b)
unnamed: U76.3, U85.6 (I0a)
unnamed: U76.6, U85.10 (I0b)
unnamed: U77.3, U85.5 (I1a)
unnamed: U77.6, U85.11 (I1b)
unnamed: U76.8, U86.6 (I0a)
unnamed: U76.11, U86.10 (I0b)
unnamed: U77.8, U86.5 (I1a)
unnamed: U77.11, U86.11 (I1b)
unnamed: U79.3, U87.6 (I0a)
unnamed: U79.6, U87.10 (I0b)
unnamed: U80.3, U87.5 (I1a)
unnamed: U80.6, U87.11 (I1b)
unnamed: U79.8, U88.6 (I0a)
unnamed: U79.11, U88.10 (I0b)
unnamed: U80.8, U88.5 (I1a)
unnamed: U80.11, U88.11 (I1b)
unnamed: U89.2, U89.6
unnamed: U54.6, U90.3 (C)
unnamed: U105.1, U106.8
unnamed: U105.2, U107.8
unnamed: U105.5, U144.4
unnamed: U105.8, U107.2
unnamed: U105.12, U161.10
unnamed: U105.13, U107.11
unnamed: U106.2, U111.13
unnamed: U106.4, U108.1
unnamed: U71.6, U106.10
unnamed: U107.3, U116.3
unnamed: U107.6, U116.2
unnamed: U108.2, U108.8
unnamed: U108.6, U117.5
unnamed: U108.10, U116.8
unnamed: U108.11, U116.5
unnamed: U109.3, U116.6
unnamed: U109.5, U110.11
unnamed: U109.6, U121.12
unnamed: U109.8, U121.10
unnamed: U110.6, U164.1
unnamed: U111.2, U120.6
unnamed: U111.8, U117.1
unnamed: U112.6, U117.4
unnamed: U56.5, U112.8
unnamed: U82.8, U112.9
unnamed: U91.3, U112.10
unnamed: U112.12, U117.2
unnamed: U113.3, U118.10
unnamed: U113.6, U118.9
unnamed: U113.8, U118.12
unnamed: U113.12, U120.11
unnamed: U113.13, U120.3
unnamed: U114.1 (0), U123.5
unnamed: U114.2 (1), U123.9
unnamed: U114.6 (5), U124.3
unnamed: U114.7 (6), U124.5
unnamed: U114.11 (9), U124.13
unnamed: U117.6, U120.2
unnamed: U118.8, U120.10
unnamed: U119.4, U121.9
unnamed: U56.2, U120.8
unnamed: U121.6, U126.4
unnamed: U56.10, U121.8
unnamed: U54.12, U122.6
unnamed: U82.5, U123.4
unnamed: U125.10, U148.2
unnamed: U54.13, U125.12, U126.5
unnamed: U127.11, U143.3
unnamed: U128.2, U144.12
unnamed: U128.8, U145.2
unnamed: U133.15 (TC), U134.10 (CET)
unnamed: U134.15 (TC), U135.10 (CET)
unnamed: U126.6, U136.1 (~Mr), U137.1 (~Mr)
unnamed: U54.11, U138.1 (~R)
unnamed: U138.10 (~S), U147.6
unnamed: U126.3, U139.9 (Cp)
unnamed: U128.12, U139.13 (D3)
unnamed: U127.3, U139.1 (~Mr)
unnamed: U142.4, U156.4
unnamed: U142.13, U155.4
unnamed: U143.4, U157.8
unnamed: U143.5, U151.3
unnamed: U89.9, U143.6
unnamed: U27.1, U148.1
unnamed: U27.10, U148.13
unnamed: U151.6, U156.13
unnamed: U152.6, U155.2
unnamed: U152.8, U157.11
unnamed: U152.12, U155.1
unnamed: U154.6, U157.5
unnamed: U154.8, U157.6
unnamed: U154.12, U157.4
unnamed: U156.5, U156.8
unnamed: U71.8, U156.12
unnamed: U164.2, U170.8
unnamed: U168.1, U168.6
unnamed: U168.2, U168.8
unnamed: U168.4, U168.11
unnamed: U54.8, U171.8
VCC: J1.1, J2.1, J3.1, J4.1, U1.20 (VCC), U8.14 (VCC), U11.20 (VCC), U17.20 (VCC), U18.20 (VCC), U19.20 (VCC), U21.6 (E2), U21.16 (VCC), U27.14 (VCC), U35.20 (VCC), U37.20 (VCC), U44.14 (VCC), U46.20 (VCC), U49.20 (VCC), U50.20 (VCC), U54.14 (VCC), U55.14 (VCC), U56.14 (VCC), U57.14 (VCC), U58.14 (VCC), U59.14 (VCC), U60.14 (VCC), U61.16 (VCC), U62.16 (VCC), U63.16 (VCC), U64.16 (VCC), U65.16 (VCC), U66.16 (VCC), U67.16 (VCC), U68.1, U68.2, U68.14 (VCC), U69.16 (VCC), U70.16 (VCC), U71.1, U71.2, U71.14 (VCC), U73.14 (VCC), U74.14 (VCC), U75.16 (VCC), U76.14 (VCC), U77.14 (VCC), U78.16 (VCC), U79.14 (VCC), U80.14 (VCC), U81.16 (VCC), U82.14 (VCC), U83.16 (VCC), U84.16 (VCC), U85.16 (VCC), U86.16 (VCC), U87.16 (VCC), U88.16 (VCC), U89.14 (VCC), U90.1 (~R), U90.4 (~S), U90.14 (VCC), U91.14 (VCC), U92.16 (VCC), U93.16 (VCC), U94.16 (VCC), U95.16 (VCC), U96.16 (VCC), U97.16 (VCC), U98.16 (VCC), U99.16 (VCC), U100.16 (VCC), U101.16 (VCC), U102.16 (VCC), U103.16 (VCC), U104.16 (VCC), U105.14 (VCC), U106.14 (VCC), U107.14 (VCC), U108.14 (VCC), U109.14 (VCC), U110.14 (VCC), U111.14 (VCC), U112.14 (VCC), U113.14 (VCC), U114.16 (VCC), U116.1, U116.14 (VCC), U117.14 (VCC), U118.14 (VCC), U119.14 (VCC), U120.14 (VCC), U121.14 (VCC), U122.14 (VCC), U123.14 (VCC), U124.14 (VCC), U125.14 (VCC), U126.14 (VCC), U127.14 (VCC), U128.14 (VCC), U129.1 (~Mr), U129.16 (VCC), U130.1 (~Mr), U130.16 (VCC), U131.1 (~Mr), U131.16 (VCC), U132.1 (~Mr), U132.16 (VCC), U133.1 (~MR), U133.16 (VCC), U134.1 (~MR), U134.16 (VCC), U135.1 (~MR), U135.16 (VCC), U136.16 (VCC), U137.16 (VCC), U138.4 (~S), U138.14 (VCC), U139.16 (VCC), U140.6 (E2), U140.16 (VCC), U141.14 (VCC), U142.14 (VCC), U143.14 (VCC), U144.14 (VCC), U145.14 (VCC), U146.14 (VCC), U147.14 (VCC), U148.14 (VCC), U149.14 (VCC), U150.14 (VCC), U151.14 (VCC), U152.14 (VCC), U153.14 (VCC), U154.14 (VCC), U155.14 (VCC), U156.14 (VCC), U157.1, U157.2, U157.3, U157.14 (VCC), U158.14 (VCC), U159.14 (VCC), U160.14 (VCC), U161.14 (VCC), U162.20 (VCC), U163.20 (VCC), U164.14 (VCC), U165.1, U165.2, U165.14 (VCC), U168.14 (VCC), U169.20 (VCC), U170.14 (VCC), U171.14 (VCC)

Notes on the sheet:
TS3: ACUM <= ACUM + MBUF
TS4: MADR <= MBUF
TS3: PCTR <= MBUF
RSEL 0 nop 1 BSW 2 RAL 3 RTL 4 RAR 5 RTR 6,7 zero
inc pc for isz instrs
TS4: MADR <= INBUS (dma addr)
TS2: MBUF <= INBUS (dma data)
TS4: MADR <= 0
sets ALU to compute MADR + 1 _JJ5 sets up the add in TS3 but does not clock into MADR at TP3 _JJ6 continues the add in TS4 then gets clocked into MADR at TP4
(efaddr_2)
TS3: ACUM <= ACUM | INBUS (io data)
gate SWREG onto INBUS * during TS3 of Group2 for OSR * while LDAD held down to load MADR * during TS2 while doing deposit
load pc for jms
TS3: ACUM <= 0
TS3: PCTR <= MADR + 1
LSB
brkcyc sets at TS1 of break cycle clears at TS4 of all cycles
(efaddr_0)
TS2: MBUF <= INBUS (swREG)
enable pc load at next pcclk
Clear ACUM for Group1 CLA at TP2
clock in new MADR at TP4 except EXAM and DEPOS cycles
asserted (low) when doing Group2 CLA
TS3 msfetch group1 IAC
MSB
TS1: MBUF <= INBUS (mem data)
(efaddr_3)
TS2: MBUF <= PCTR
load pc for indir jmp
load pc for dir jmp
TS4: MADR <= efaddr
(efaddr_1)
TS4: MADR <= PCTR
load pc when halted for ldad/exam/depos
load pc for intak
low when doing Group2 with OSR bit low blocking SR coming in on INBUS
TS3: ACUM <= ACUM & MBUF
TS3: PCTR <= efaddr
swEXAM: MADR <= MADR + 1
(efaddr_4)

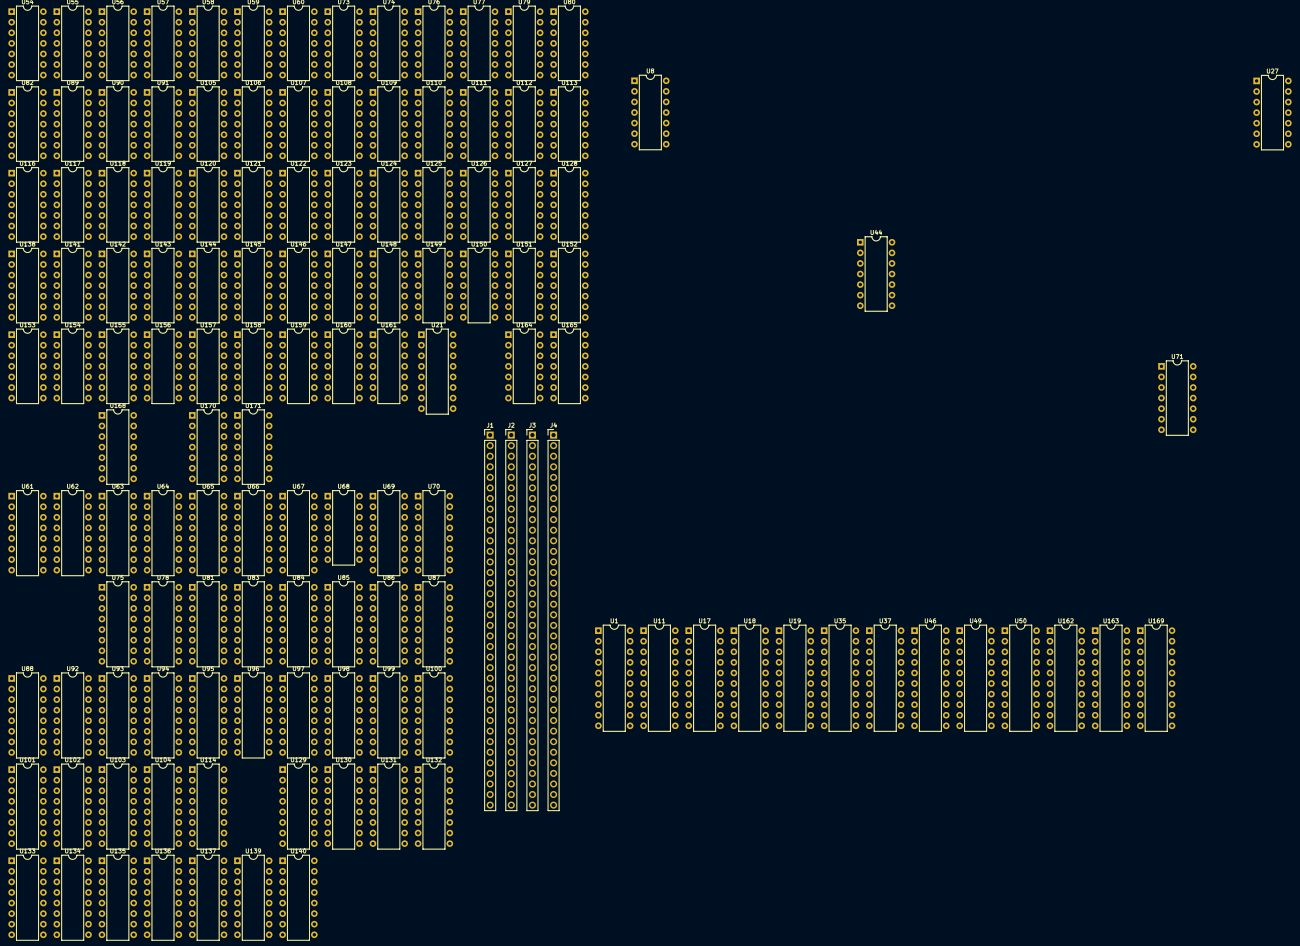
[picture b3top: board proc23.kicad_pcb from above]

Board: 2 copper layers, 132 parts (0 on the bottom side), 512 nets, no tracks yet.
